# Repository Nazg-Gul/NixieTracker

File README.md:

NixieTracker
============

This is a nixie tube based display for number of opened bugs in Blender tracker.

The hardware itself doesn't care at all which three digits it displays so it'll
be totally simple to adopt it to something else.

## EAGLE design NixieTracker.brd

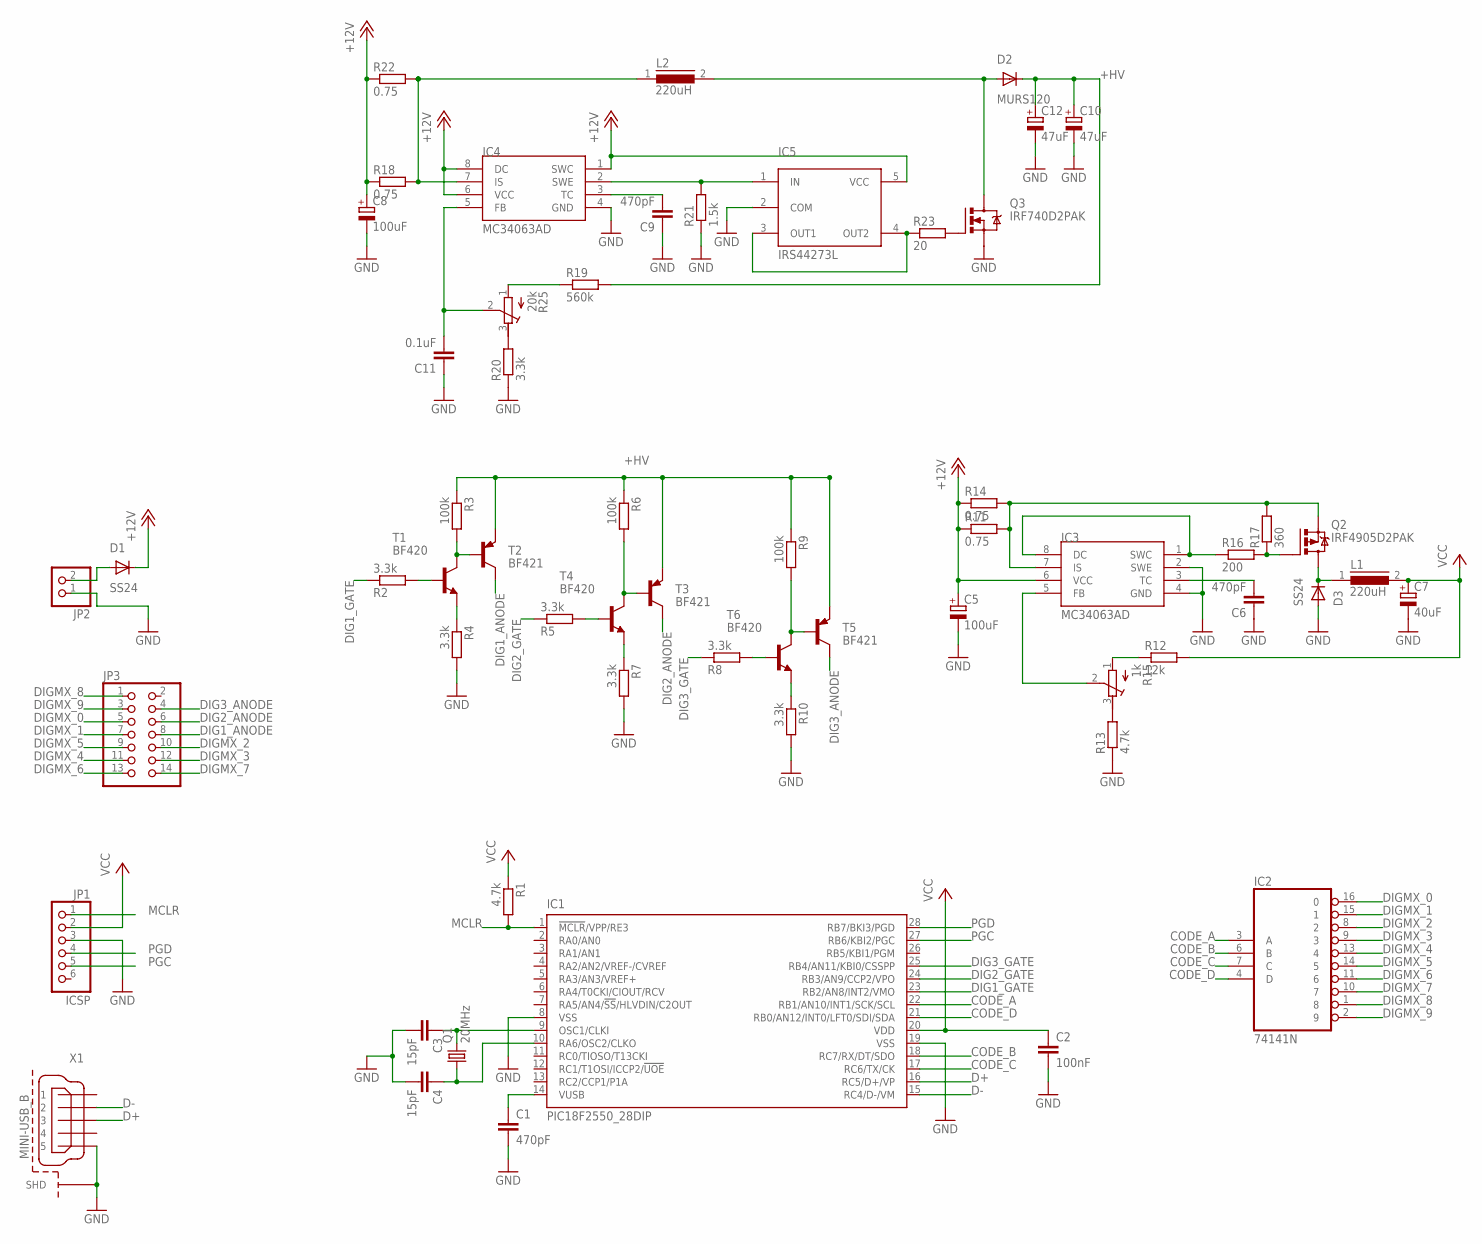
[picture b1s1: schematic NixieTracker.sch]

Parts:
C1: 470pF; C050-024X044
C2: 100nF; C050-024X044
C3, C4: 15pF; C050-024X044
C5, C8: 100uF; D/7343-31R
C6, C9: 470pF; C1206K
C7: 40uF; C/6032-28R
C10, C12: 47uF; SANYO-OSCON_F13
C11: 0.1uF; C1206K
D1, D3: SS24; DO214AA
D2: MURS120; DO214AA
IC1: PIC18F2550_28DIP; DIL28-3
IC2: 74141N; DIL16
IC3, IC4: MC34063AD; SOIC8
IC5: IRS44273L; SOT23-5
JP1: ICSP; 1X06
JP2: PINHD-1X2; 1X02
JP3: PINHD-2X7; 2X07
L1, L2: 220uH; DR125
Q1: 20MHz; HC49/S
Q2: IRF4905D2PAK; D2PAK
Q3: IRF740D2PAK; D2PAK
R1: 4.7k; 0207/2V
R2, R5, R8: 3.3k; 0207/2V
R3, R6, R9: 100k; 0207/5V
R4, R7, R10: 3.3k; 0207/7
R11, R14, R18, R22: 0.75; R1206
R12: 12k; R1206
R13: 4.7k; R1206
R15: 1k; RTRIM4G/J
R16: 200; R1206
R17: 360; R1206
R19: 560k; R1206
R20: 3.3k; R1206
R21: 1.5k; R1206
R23: 20; R1206
R25: 20k; RTRIM4G/J
T1, T4, T6: BF420; TO92-ECB
T2, T3, T5: BF421; TO92-ECB
X1: MINI-USB_B; MINI-USB-B

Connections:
+12V: C5.+, C8.+, D1.C, IC3.6 (VCC), IC4.1 (SWC), IC4.6 (VCC), IC4.8 (DC), IC5.5 (VCC), R11.1, R14.1, R18.1, R22.1
+HV: C10.+, C12.+, D2.C, R3.1, R6.1, R9.1, R19.2, T2.E, T3.E, T5.E
CODE_A: IC1.22 (RB1/AN10/INT1/SCK/SCL), IC2.3 (A)
CODE_B: IC1.18 (RC7/RX/DT/SDO), IC2.6 (B)
CODE_C: IC1.17 (RC6/TX/CK), IC2.7 (C)
CODE_D: IC1.21 (RB0/AN12/INT0/LFT0/SDI/SDA), IC2.4 (D)
D+: IC1.16 (RC5/D+/VP), X1.3
D-: IC1.15 (RC4/D-/VM), X1.2
DIG1_ANODE: JP3.8, T2.C
DIG1_GATE: IC1.23 (RB2/AN8/INT2/VMO), R2.1
DIG2_ANODE: JP3.6, T3.C
DIG2_GATE: IC1.24 (RB3/AN9/CCP2/VPO), R5.1
DIG3_ANODE: JP3.4, T5.C
DIG3_GATE: IC1.25 (RB4/AN11/KBI0/CSSPP), R8.1
DIGMX_0: IC2.16 (0), JP3.5
DIGMX_1: IC2.15 (1), JP3.7
DIGMX_2: IC2.8 (2), JP3.10
DIGMX_3: IC2.9 (3), JP3.12
DIGMX_4: IC2.13 (4), JP3.11
DIGMX_5: IC2.14 (5), JP3.9
DIGMX_6: IC2.11 (6), JP3.13
DIGMX_7: IC2.10 (7), JP3.14
DIGMX_8: IC2.1 (8), JP3.1
DIGMX_9: IC2.2 (9), JP3.3
GND: C1.2, C2.2, C3.2, C4.2, C5.-, C6.1, C7.-, C8.-, C9.1, C10.-, C11.1, C12.-, D3.A, IC1.8 (VSS), IC1.19 (VSS), IC2.12 (GND), IC3.2 (SWE), IC3.4 (GND), IC4.4 (GND), IC5.2 (COM), JP1.3, JP2.1, Q3.3 (S), R4.2, R7.2, R10.2, R13.1, R20.1, R21.1, X1.5, X1.M1 (SHD), X1.M2 (SHD), X1.M3 (SHD), X1.M4 (SHD)
MCLR: IC1.1 (!MCLR!/VPP/RE3), JP1.1, R1.2
unnamed: C1.1, IC1.14 (VUSB)
unnamed: C3.1, IC1.9 (OSC1/CLKI), Q1.2
unnamed: C4.1, IC1.10 (RA6/OSC2/CLKO), Q1.1
unnamed: R3.2, T1.C, T2.B
unnamed: R2.2, T1.B
unnamed: R4.1, T1.E
unnamed: R6.2, T3.B, T4.C
unnamed: R7.1, T4.E
unnamed: R5.2, T4.B
unnamed: R9.2, T5.B, T6.C
unnamed: R10.1, T6.E
unnamed: R8.2, T6.B
unnamed: C6.2, IC3.3 (TC)
unnamed: IC3.5 (FB), R15.2 (S)
unnamed: D2.A, L2.2, Q3.4 (D)
unnamed: D1.A, JP2.2
unnamed: D3.C, L1.1, Q2.4 (D)
unnamed: IC3.7 (IS), Q2.3 (S), R11.2, R14.2, R17.2
unnamed: Q2.1 (G), R16.2, R17.1
unnamed: IC3.1 (SWC), IC3.8 (DC), R16.1
unnamed: R13.2, R15.3 (E)
unnamed: R12.1, R15.1 (A)
unnamed: IC4.7 (IS), L2.1, R18.2, R22.2
unnamed: C9.2, IC4.3 (TC)
unnamed: C11.2, IC4.5 (FB), R25.2 (S)
unnamed: IC4.2 (SWE), IC5.1 (IN), R21.2
unnamed: Q3.1 (G), R23.2
unnamed: IC5.3 (OUT1), IC5.4 (OUT2), R23.1
unnamed: R19.1, R25.1 (A)
unnamed: R20.2, R25.3 (E)
PGC: IC1.27 (RB6/KBI2/PGC), JP1.5
PGD: IC1.28 (RB7/BKI3/PGD), JP1.4
VCC: C2.1, C7.+, IC1.20 (VDD), IC2.5 (VCC), JP1.2, L1.2, R1.1, R12.2

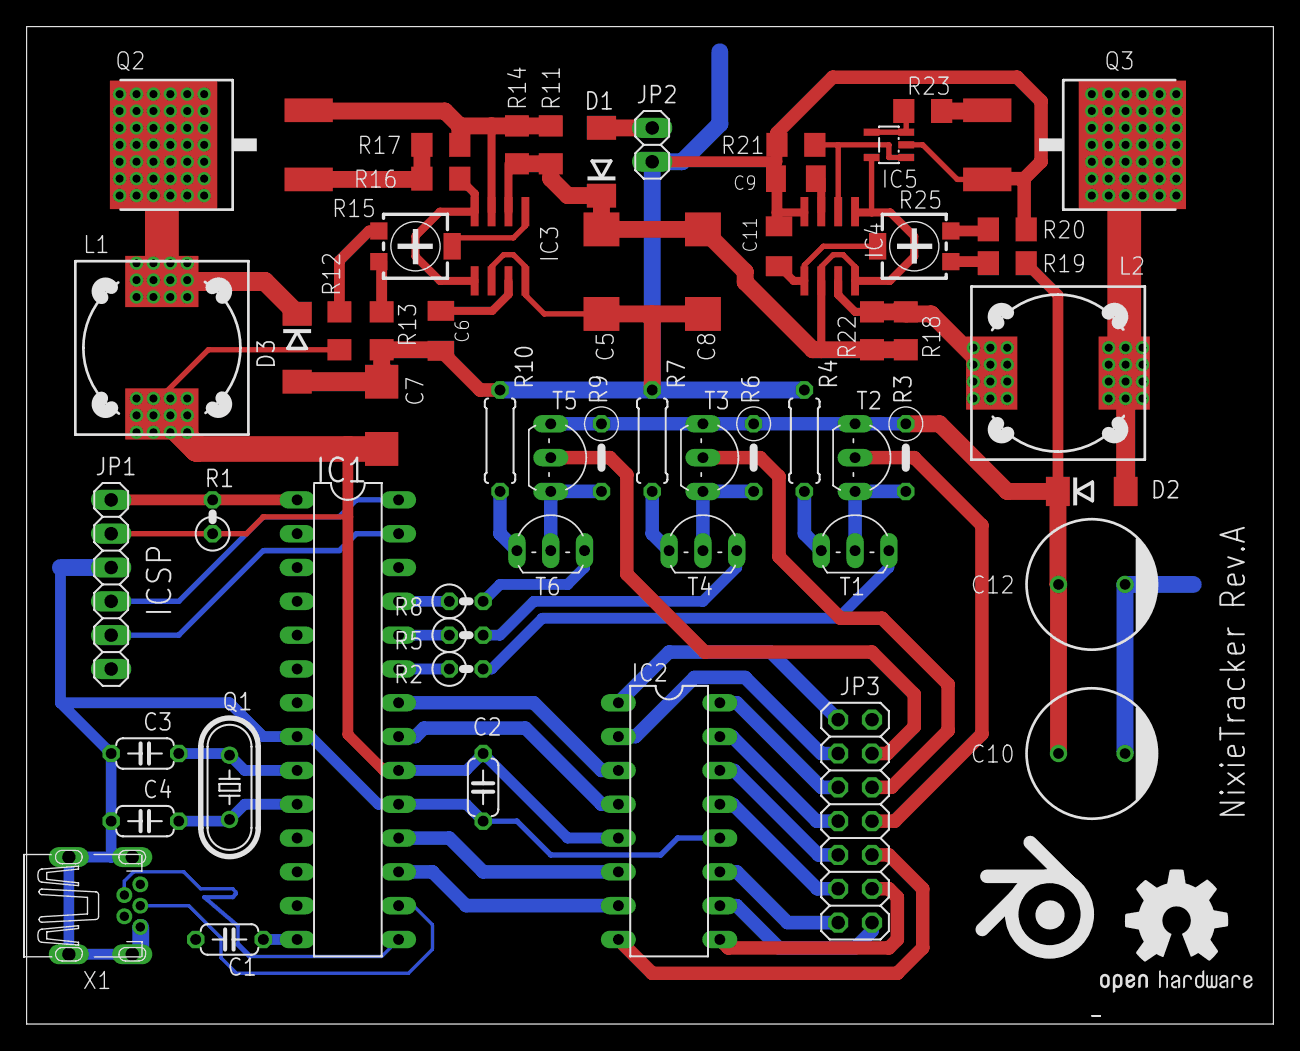
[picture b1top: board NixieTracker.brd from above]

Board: 2 copper layers, 93.7 x 74.9 mm, 60 parts (0 on the bottom side), 59 nets.

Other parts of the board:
U$1: OSHW1

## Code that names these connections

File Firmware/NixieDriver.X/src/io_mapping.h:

/* Copyright (C) 2014 Sergey Sharybin <sergey@blender.org>
 *
 * Permission is hereby granted, free of charge, to any person obtaining a copy
 * of this software and associated documentation files (the "Software"), to
 * deal in the Software without restriction, including without limitation the
 * rights to use, copy, modify, merge, publish, distribute, sublicense, and/or
 * sell copies of the Software, and to permit persons to whom the Software is
 * furnished to do so, subject to the following conditions:
 *
 *The above copyright notice and this permission notice shall be included in
 * all copies or substantial portions of the Software.
 *
 * THE SOFTWARE IS PROVIDED "AS IS", WITHOUT WARRANTY OF ANY KIND, EXPRESS OR
 * IMPLIED, INCLUDING BUT NOT LIMITED TO THE WARRANTIES OF MERCHANTABILITY,
 * FITNESS FOR A PARTICULAR PURPOSE AND NONINFRINGEMENT. IN NO EVENT SHALL THE
 * AUTHORS OR COPYRIGHT HOLDERS BE LIABLE FOR ANY CLAIM, DAMAGES OR OTHER
 * LIABILITY, WHETHER IN AN ACTION OF CONTRACT, TORT OR OTHERWISE, ARISING
 * FROM, OUT OF OR IN CONNECTION WITH THE SOFTWARE OR THE USE OR OTHER DEALINGS
 * IN THE SOFTWARE.
 */

#ifndef __IO_MAPPING_H__
#define __IO_MAPPING_H__

/* We've optimized the routes on PCB, so now we suffer in the firmware by
 * writing to the individual bits
 */

/* Decimal code which is passed to the digital decoder. */
// RIP one of the IO pins...
#define BIN_CODE_0 PORTBbits.RB1
//#define BIN_CODE_0 PORTAbits.RA5
#define BIN_CODE_1 PORTCbits.RC7
#define BIN_CODE_2 PORTCbits.RC6
#define BIN_CODE_3 PORTBbits.RB0

#define BIN_CODE_SEND_CODE(a, b, c, d) { \
    BIN_CODE_0 = a; \
    BIN_CODE_1 = b; \
    BIN_CODE_2 = c; \
    BIN_CODE_3 = d; \
  } (void) 0

#define BIN_CODE_SEND_DIGIT(digit) { \
    BIN_CODE_SEND_CODE(digit & 1, \
                       (digit >> 1) & 1, \
                       (digit >> 2) & 1, \
                       (digit >> 3) & 1);\
  } (void) 0

#define BIN_CODE_SEND_CLOSE() \
  BIN_CODE_SEND_CODE(1, 1, 1, 1)

/* Digit number, for multiplexing, defines which transistor gate is open. */
// RIP one more of the IO pins...
#define DIG_GATE_0 PORTBbits.RB2
//#define DIG_GATE_0 PORTBbits.RB5
#define DIG_GATE_1 PORTBbits.RB3
#define DIG_GATE_2 PORTBbits.RB4

#define DIG_GATE_OPEN(gate) DIG_GATE_ ## gate = 1
#define DIG_GATE_CLOSE(gate) DIG_GATE_ ## gate = 0

#endif  /* __IO_MAPPING_H__ */

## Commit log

2015-01-11 Initial commit of blender tracker nixie display
